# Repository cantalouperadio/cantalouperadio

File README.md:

# Cantaloupe Radio Factory Radio Retrofit Platform

This project contains integrated hardware and firmware to allow stealthy, tight integrations of modern audio technology into factory classic car radios.

TODO lots more to write and explain...

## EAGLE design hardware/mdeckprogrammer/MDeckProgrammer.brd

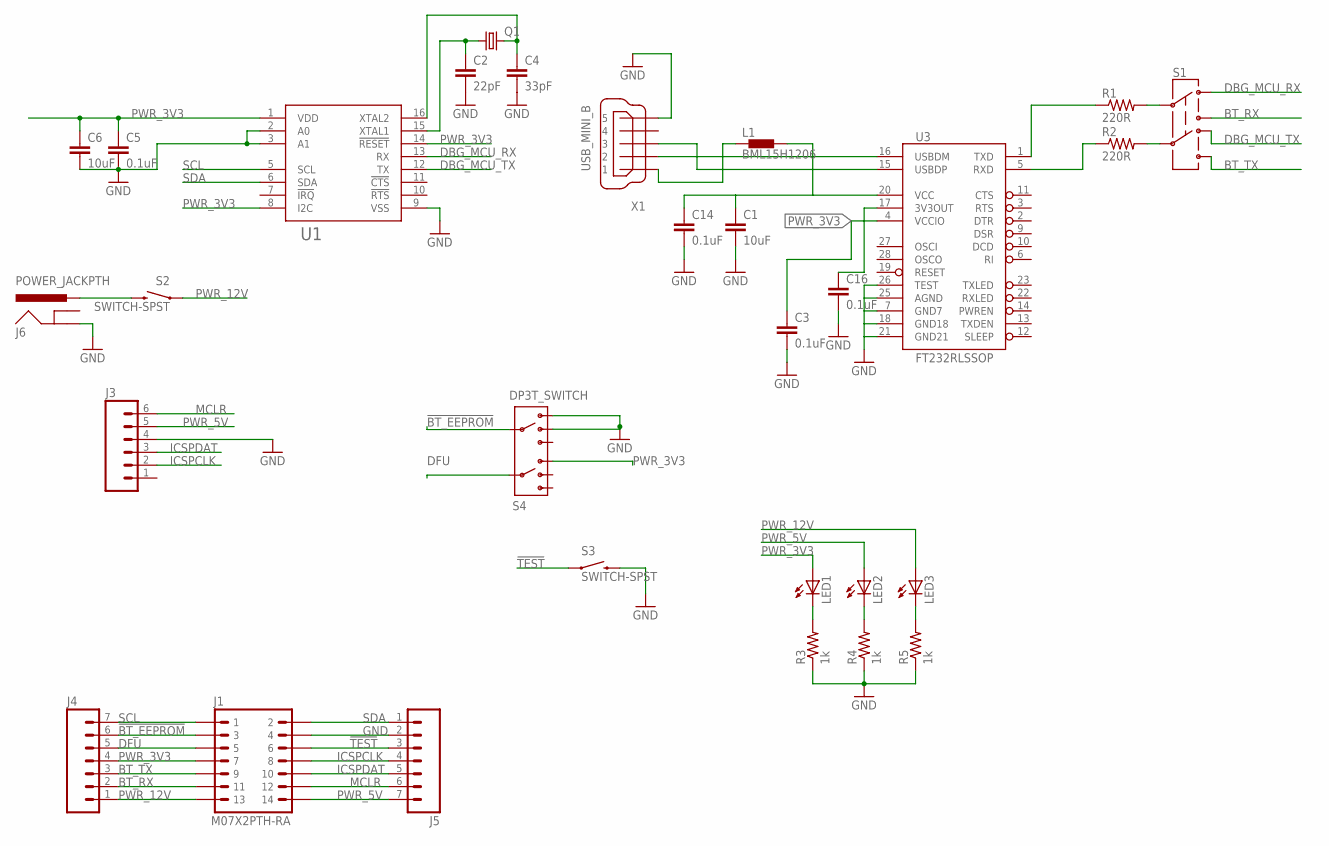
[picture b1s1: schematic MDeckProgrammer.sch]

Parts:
C1, C6: 10uF; 1206
C2: 22pF; 1206
C3, C5, C14, C16: 0.1uF; 1206
C4: 33pF; 1206
J1: M07X2PTH-RA; JST-14-PUD-PTH
J3: M06HARWIN_RA; 1X06_RA
J4, J5: M07; 1X07
J6: POWER_JACKPTH; POWER_JACK_PTH
L1: BML15H1206; 1206
LED1, LED2, LED3: LEDCHIPLED_1206; CHIPLED_1206
Q1: CRYSTALHC49S; HC49/S
R1, R2: 220R; 1206
R3, R4, R5: 1k; 1206
S1: SWITCH-DPDTPTH; MSS22
S2, S3: SWITCH-SPST; GF-123-0054
S4: DP3T_SWITCH; EG2301A
U1: SC16IS740TSSOP16; TSSOP16
U3: FT232RLSSOP; SSOP28DB
X1: USB_MINI_B; USB_MINI_B_PTH

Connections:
!BT_EEPROM: J1.P$3 (3), J4.6, S4.P$3 (COMA)
!TEST: J1.P$6 (6), J5.3, S3.P$1 (1)
BT_RX: J1.P$11 (11), J4.2, S1.3
BT_TX: J1.P$9 (9), J4.3, S1.6
DBG_MCU_RX: S1.1, U1.13 (RX)
DBG_MCU_TX: S1.4, U1.12 (TX)
DFU: J1.P$5 (5), J4.5, S4.P$7 (COMB)
GND: C1.2, C2.2, C3.2, C4.2, C5.2, C6.2, C14.2, C16.2, J1.P$4 (4), J3.4, J5.2, J6.GND, R3.1, R4.1, R5.1, S3.P$2 (2), S4.P$1 (A1), S4.P$2 (A2), U1.2 (A0), U1.3 (A1), U1.9 (VSS), U3.7 (GND7), U3.18 (GND18), U3.21 (GND21), U3.25 (AGND), U3.26 (TEST), X1.5
ICSPCLK: J1.P$8 (8), J3.2, J5.4
ICSPDAT: J1.P$10 (10), J3.3, J5.5
MCLR: J1.P$12 (12), J3.6, J5.6
unnamed: R1.2, S1.2
unnamed: R2.2, S1.5
unnamed: C2.1, Q1.1, U1.15 (XTAL1)
unnamed: C4.1, Q1.2, U1.16 (XTAL2)
unnamed: J6.PWR, S2.P$2 (2)
unnamed: R1.1, U3.1 (TXD)
unnamed: R2.1, U3.5 (RXD)
unnamed: U3.15 (USBDP), X1.3
unnamed: U3.16 (USBDM), X1.2
unnamed: LED1.C, R3.2
unnamed: L1.1, X1.1
unnamed: C1.1, C14.1, L1.2, U3.20 (VCC)
unnamed: LED2.C, R4.2
unnamed: C16.1, U3.17 (3V3OUT)
unnamed: LED3.C, R5.2
PWR_3V3: C3.1, C5.1, C6.1, J1.P$7 (7), J4.4, LED1.A, S4.P$5 (B1), U1.1 (VDD), U1.8 (I2C), U1.14 (!RESET), U3.4 (VCCIO)
PWR_5V: J1.P$14 (14), J3.5, J5.7, LED2.A
PWR_12V: J1.P$13 (13), J4.1, LED3.A, S2.P$1 (1)
SCL: J1.P$1 (1), J4.7, U1.5 (SCL)
SDA: J1.P$2 (2), J5.1, U1.6 (SDA)

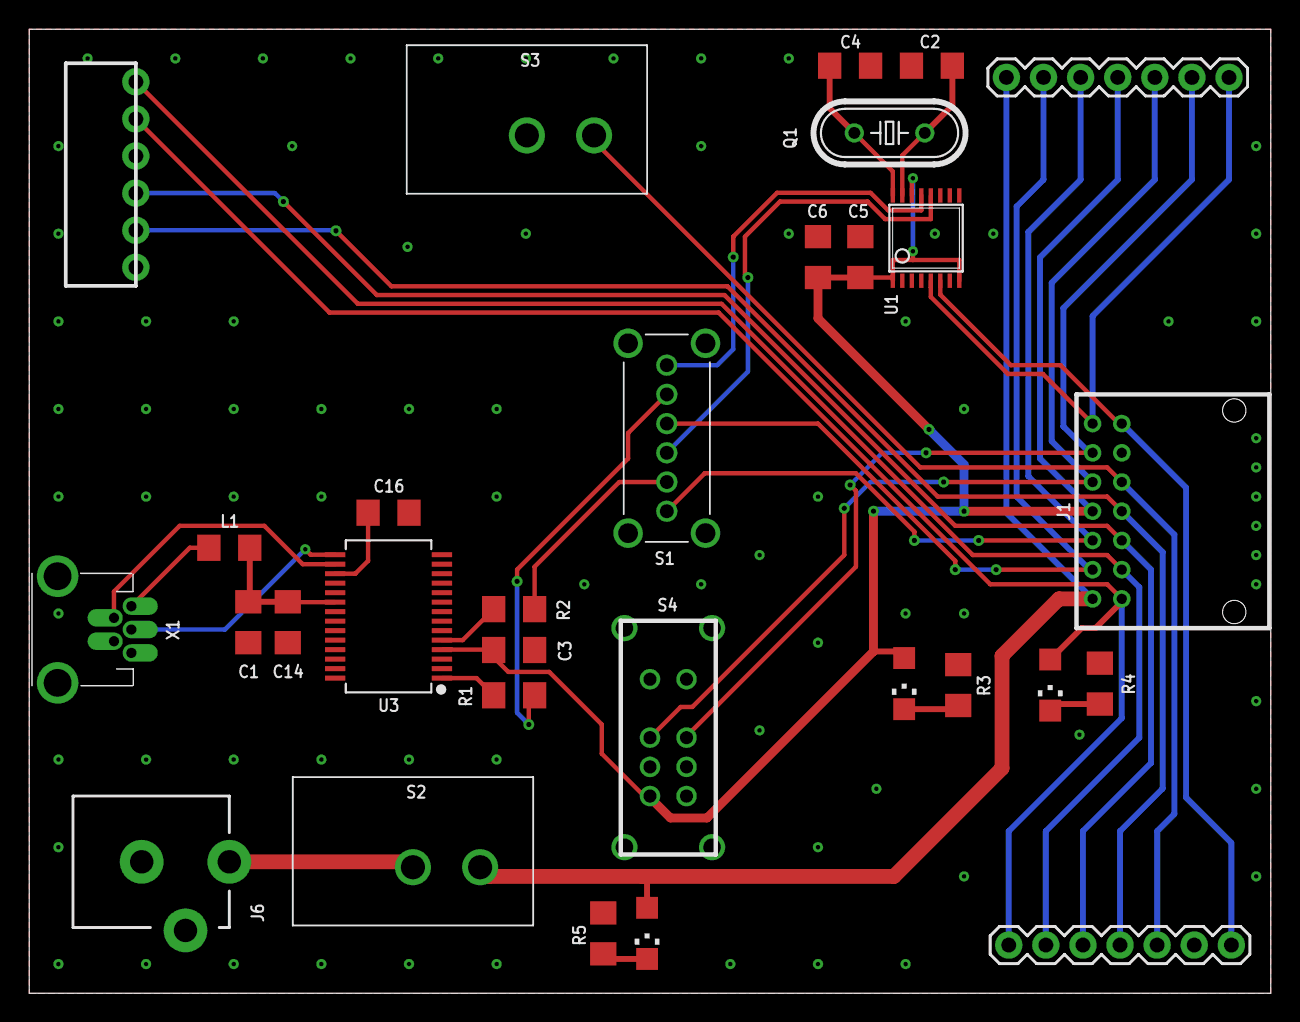
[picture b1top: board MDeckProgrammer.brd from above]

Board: 2 copper layers, 85.0 x 66.0 mm, 30 parts (0 on the bottom side), 31 nets.

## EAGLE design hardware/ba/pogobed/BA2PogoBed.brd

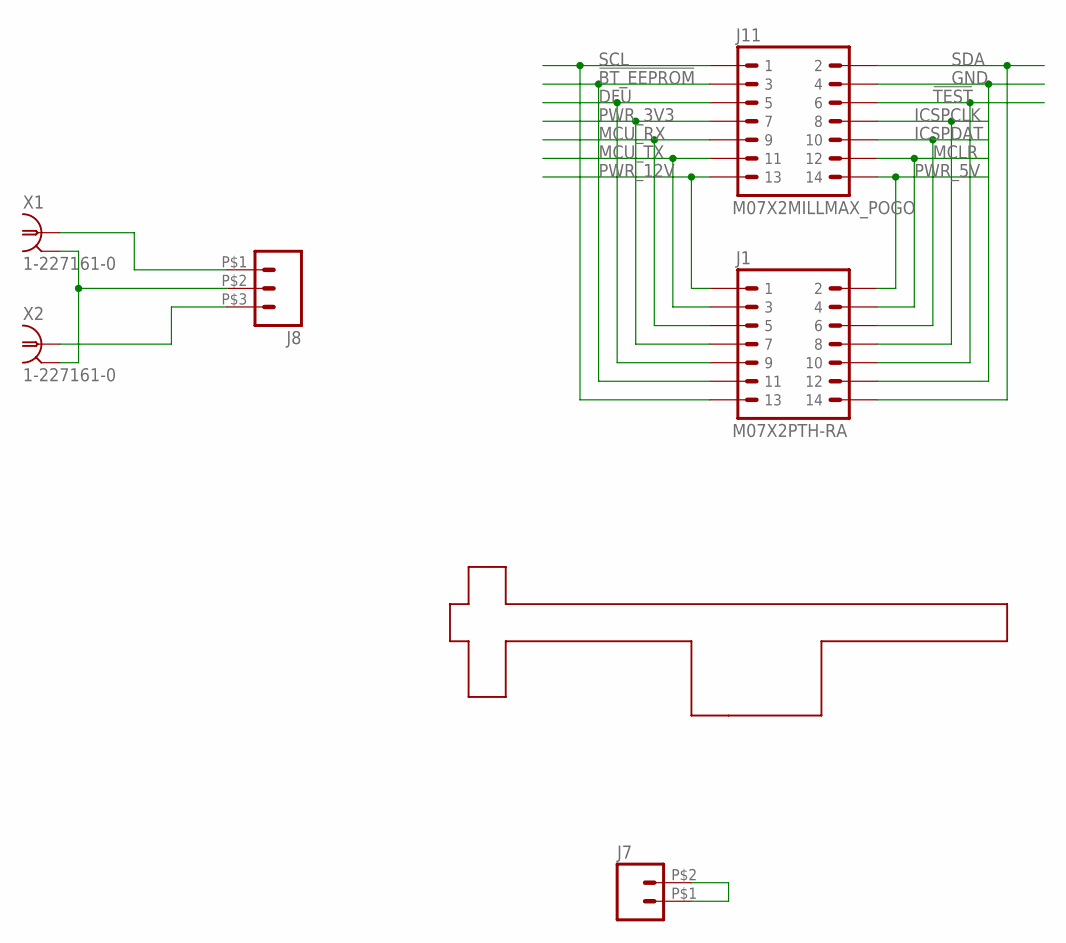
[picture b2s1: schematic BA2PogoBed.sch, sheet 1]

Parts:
J1: M07X2PTH-RA; JST-14-PUD-PTH
J7: M02; MILLMAX_838_1X2
J8: M03; MILLMAX_836_1X3
J11: M07X2MILLMAX_POGO; MILLMAX_838_7X2
M1: TOGGLE_CLAMP_LARGE
X1, X2: 1-227161-0; AMP_227161

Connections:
!BT_EEPROM: J1.P$11 (11), J11.P$3 (3)
!TEST: J1.P$10 (10), J11.P$6 (6)
DFU: J1.P$9 (9), J11.P$5 (5)
GND: J1.P$12 (12), J11.P$4 (4)
ICSPCLK: J1.P$8 (8), J11.P$8 (8)
ICSPDAT: J1.P$6 (6), J11.P$10 (10)
MCLR: J1.P$4 (4), J11.P$12 (12)
MCU_RX: J1.P$5 (5), J11.P$9 (9)
MCU_TX: J1.P$3 (3), J11.P$11 (11)
unnamed: J7.P$1 (1), J7.P$2 (2)
unnamed: J8.P$2 (2), X1.2, X2.2
unnamed: J8.P$1 (1), X1.1
unnamed: J8.P$3 (3), X2.1
PWR_3V3: J1.P$7 (7), J11.P$7 (7)
PWR_5V: J1.P$2 (2), J11.P$14 (14)
PWR_12V: J1.P$1 (1), J11.P$13 (13)
SCL: J1.P$13 (13), J11.P$1 (1)
SDA: J1.P$14 (14), J11.P$2 (2)

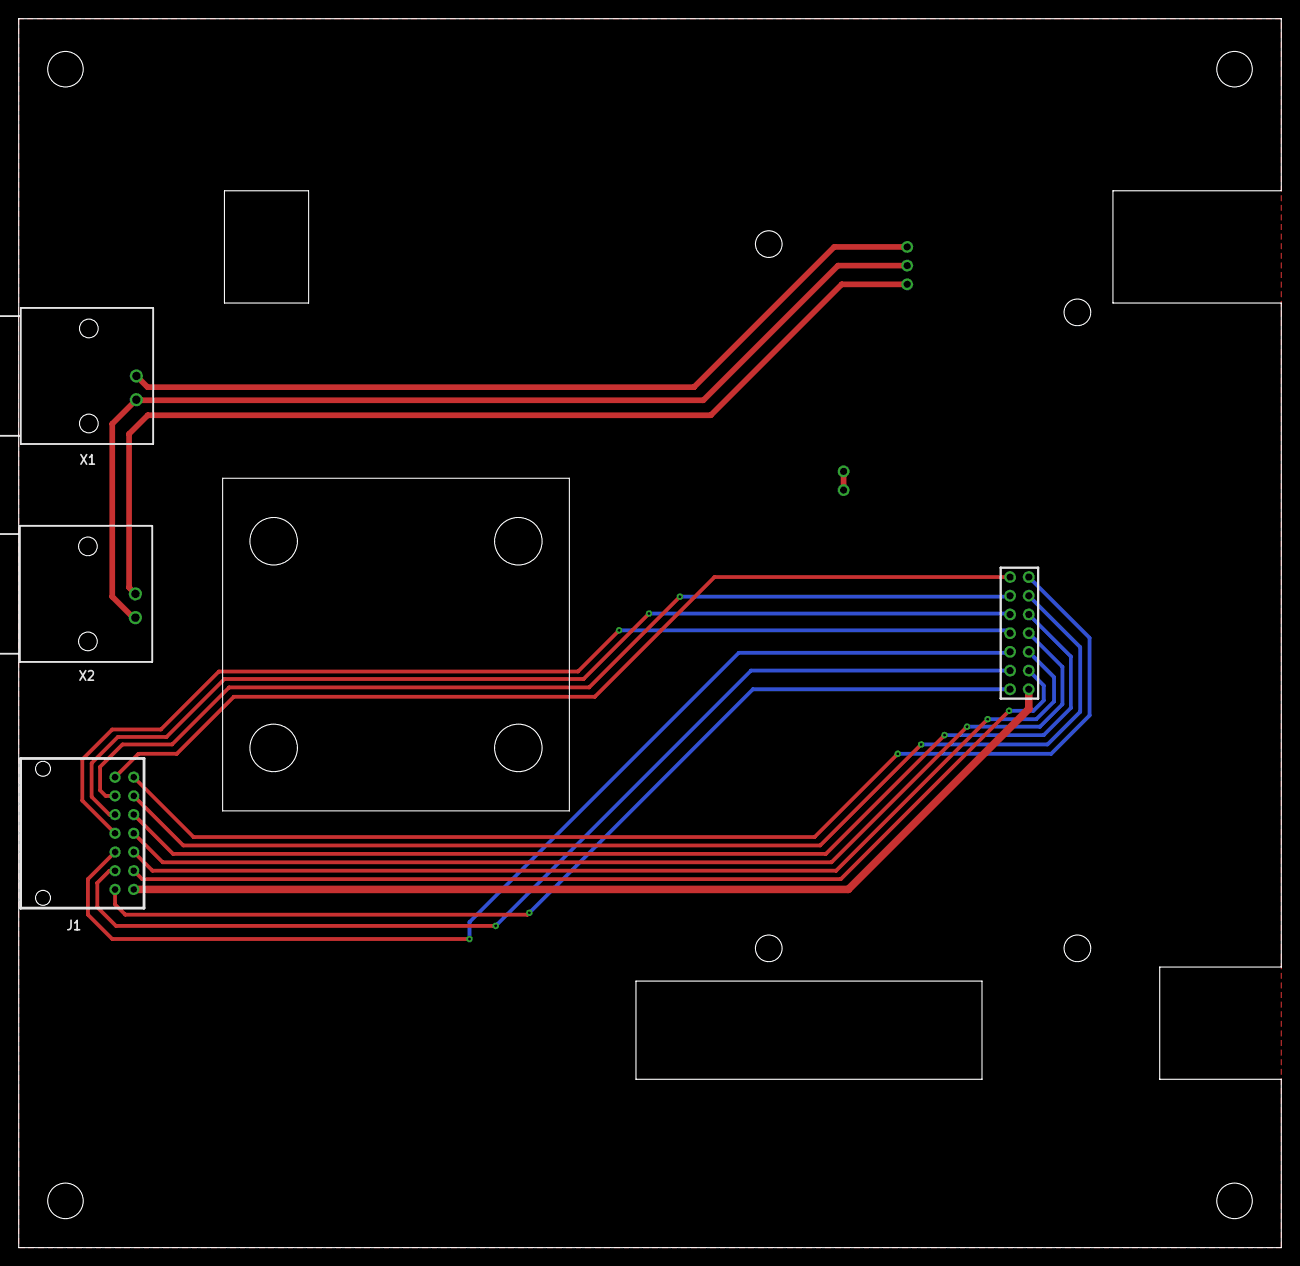
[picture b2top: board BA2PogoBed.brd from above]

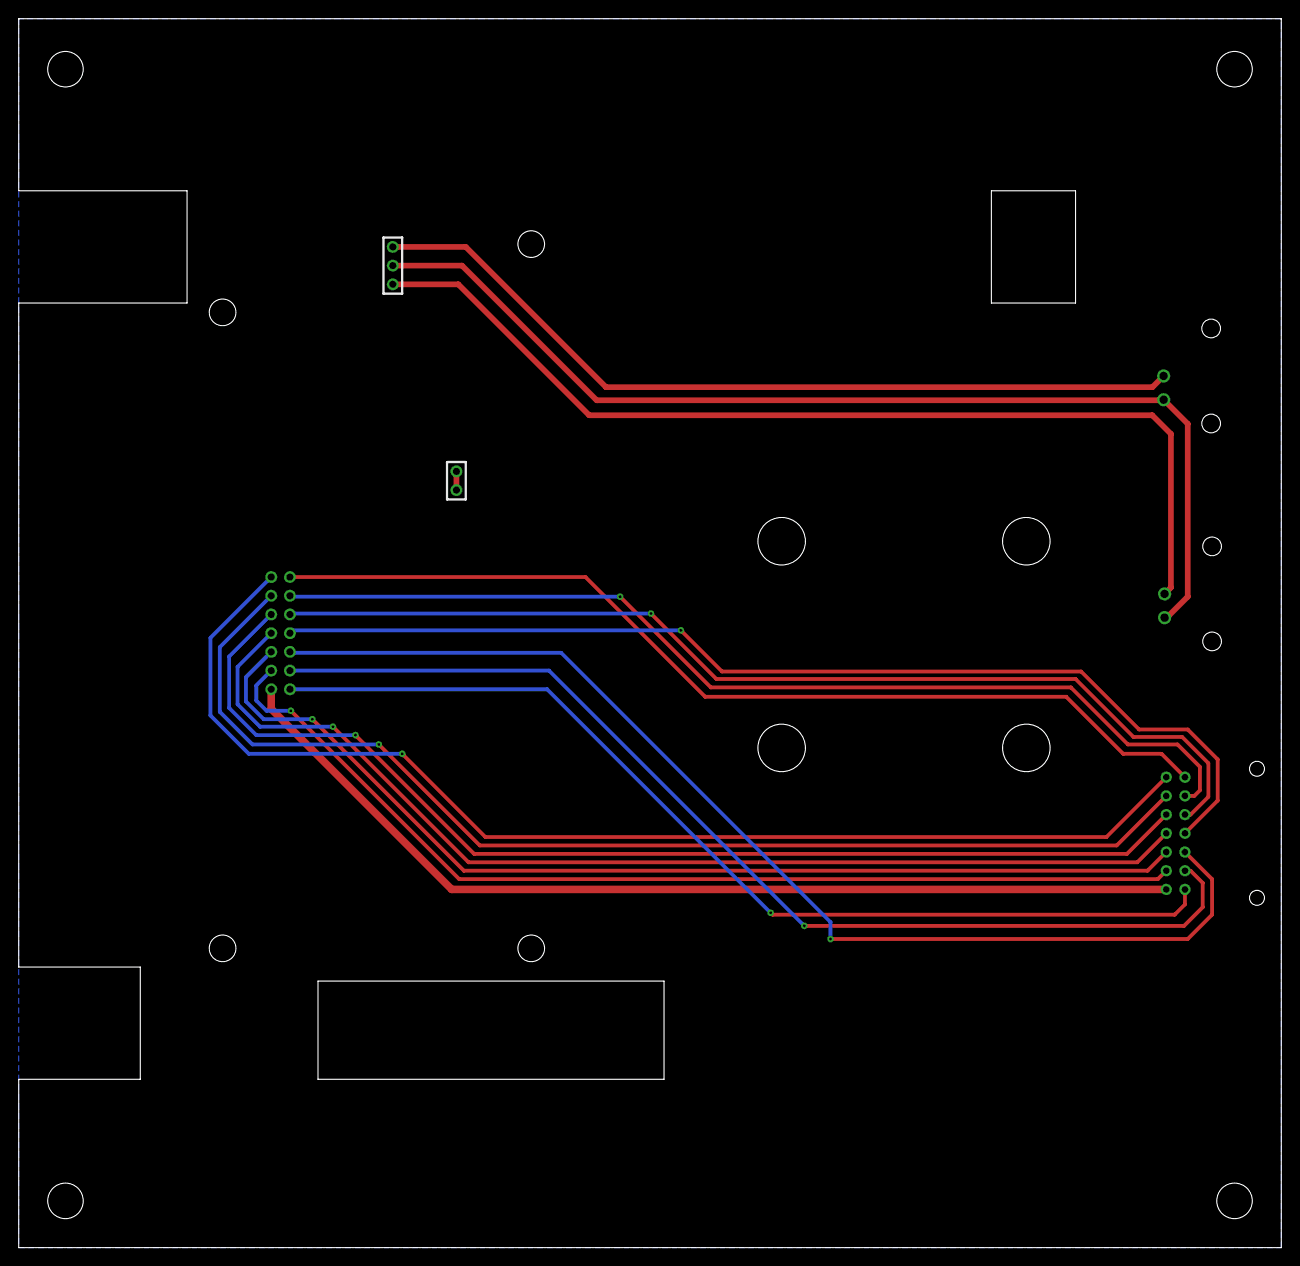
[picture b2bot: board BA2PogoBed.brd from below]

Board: 2 copper layers, 135.0 x 131.4 mm, 7 parts (2 on the bottom side), 18 nets.

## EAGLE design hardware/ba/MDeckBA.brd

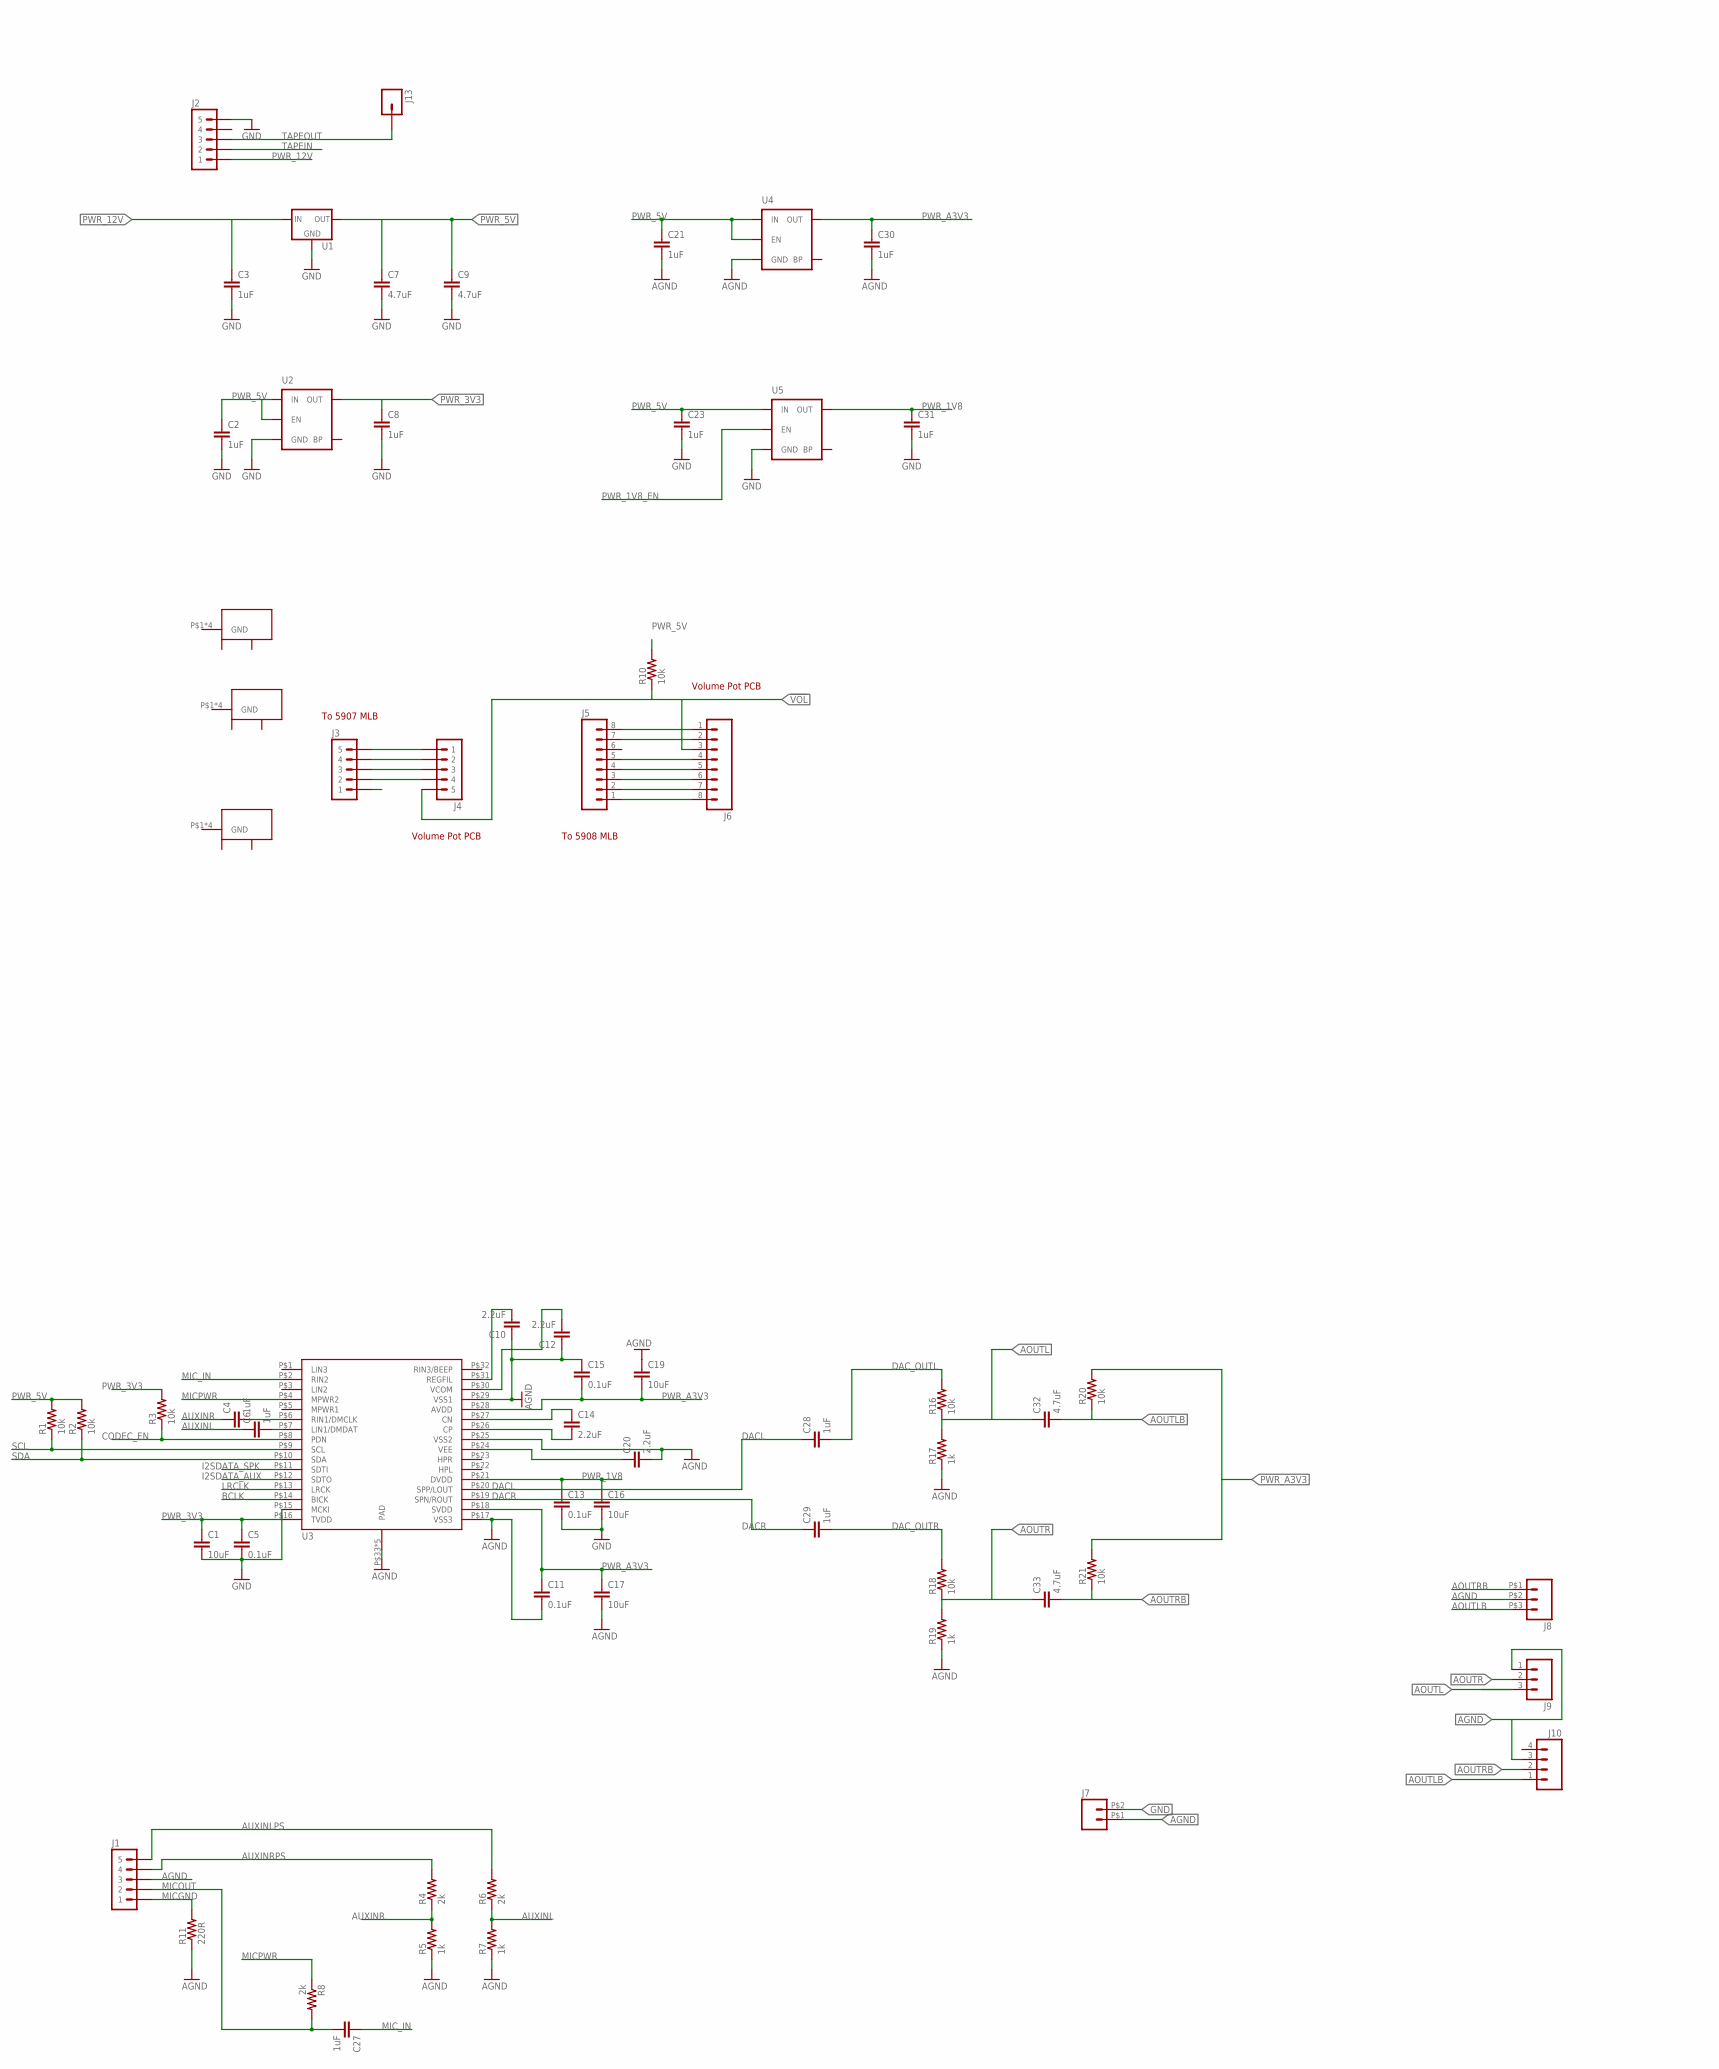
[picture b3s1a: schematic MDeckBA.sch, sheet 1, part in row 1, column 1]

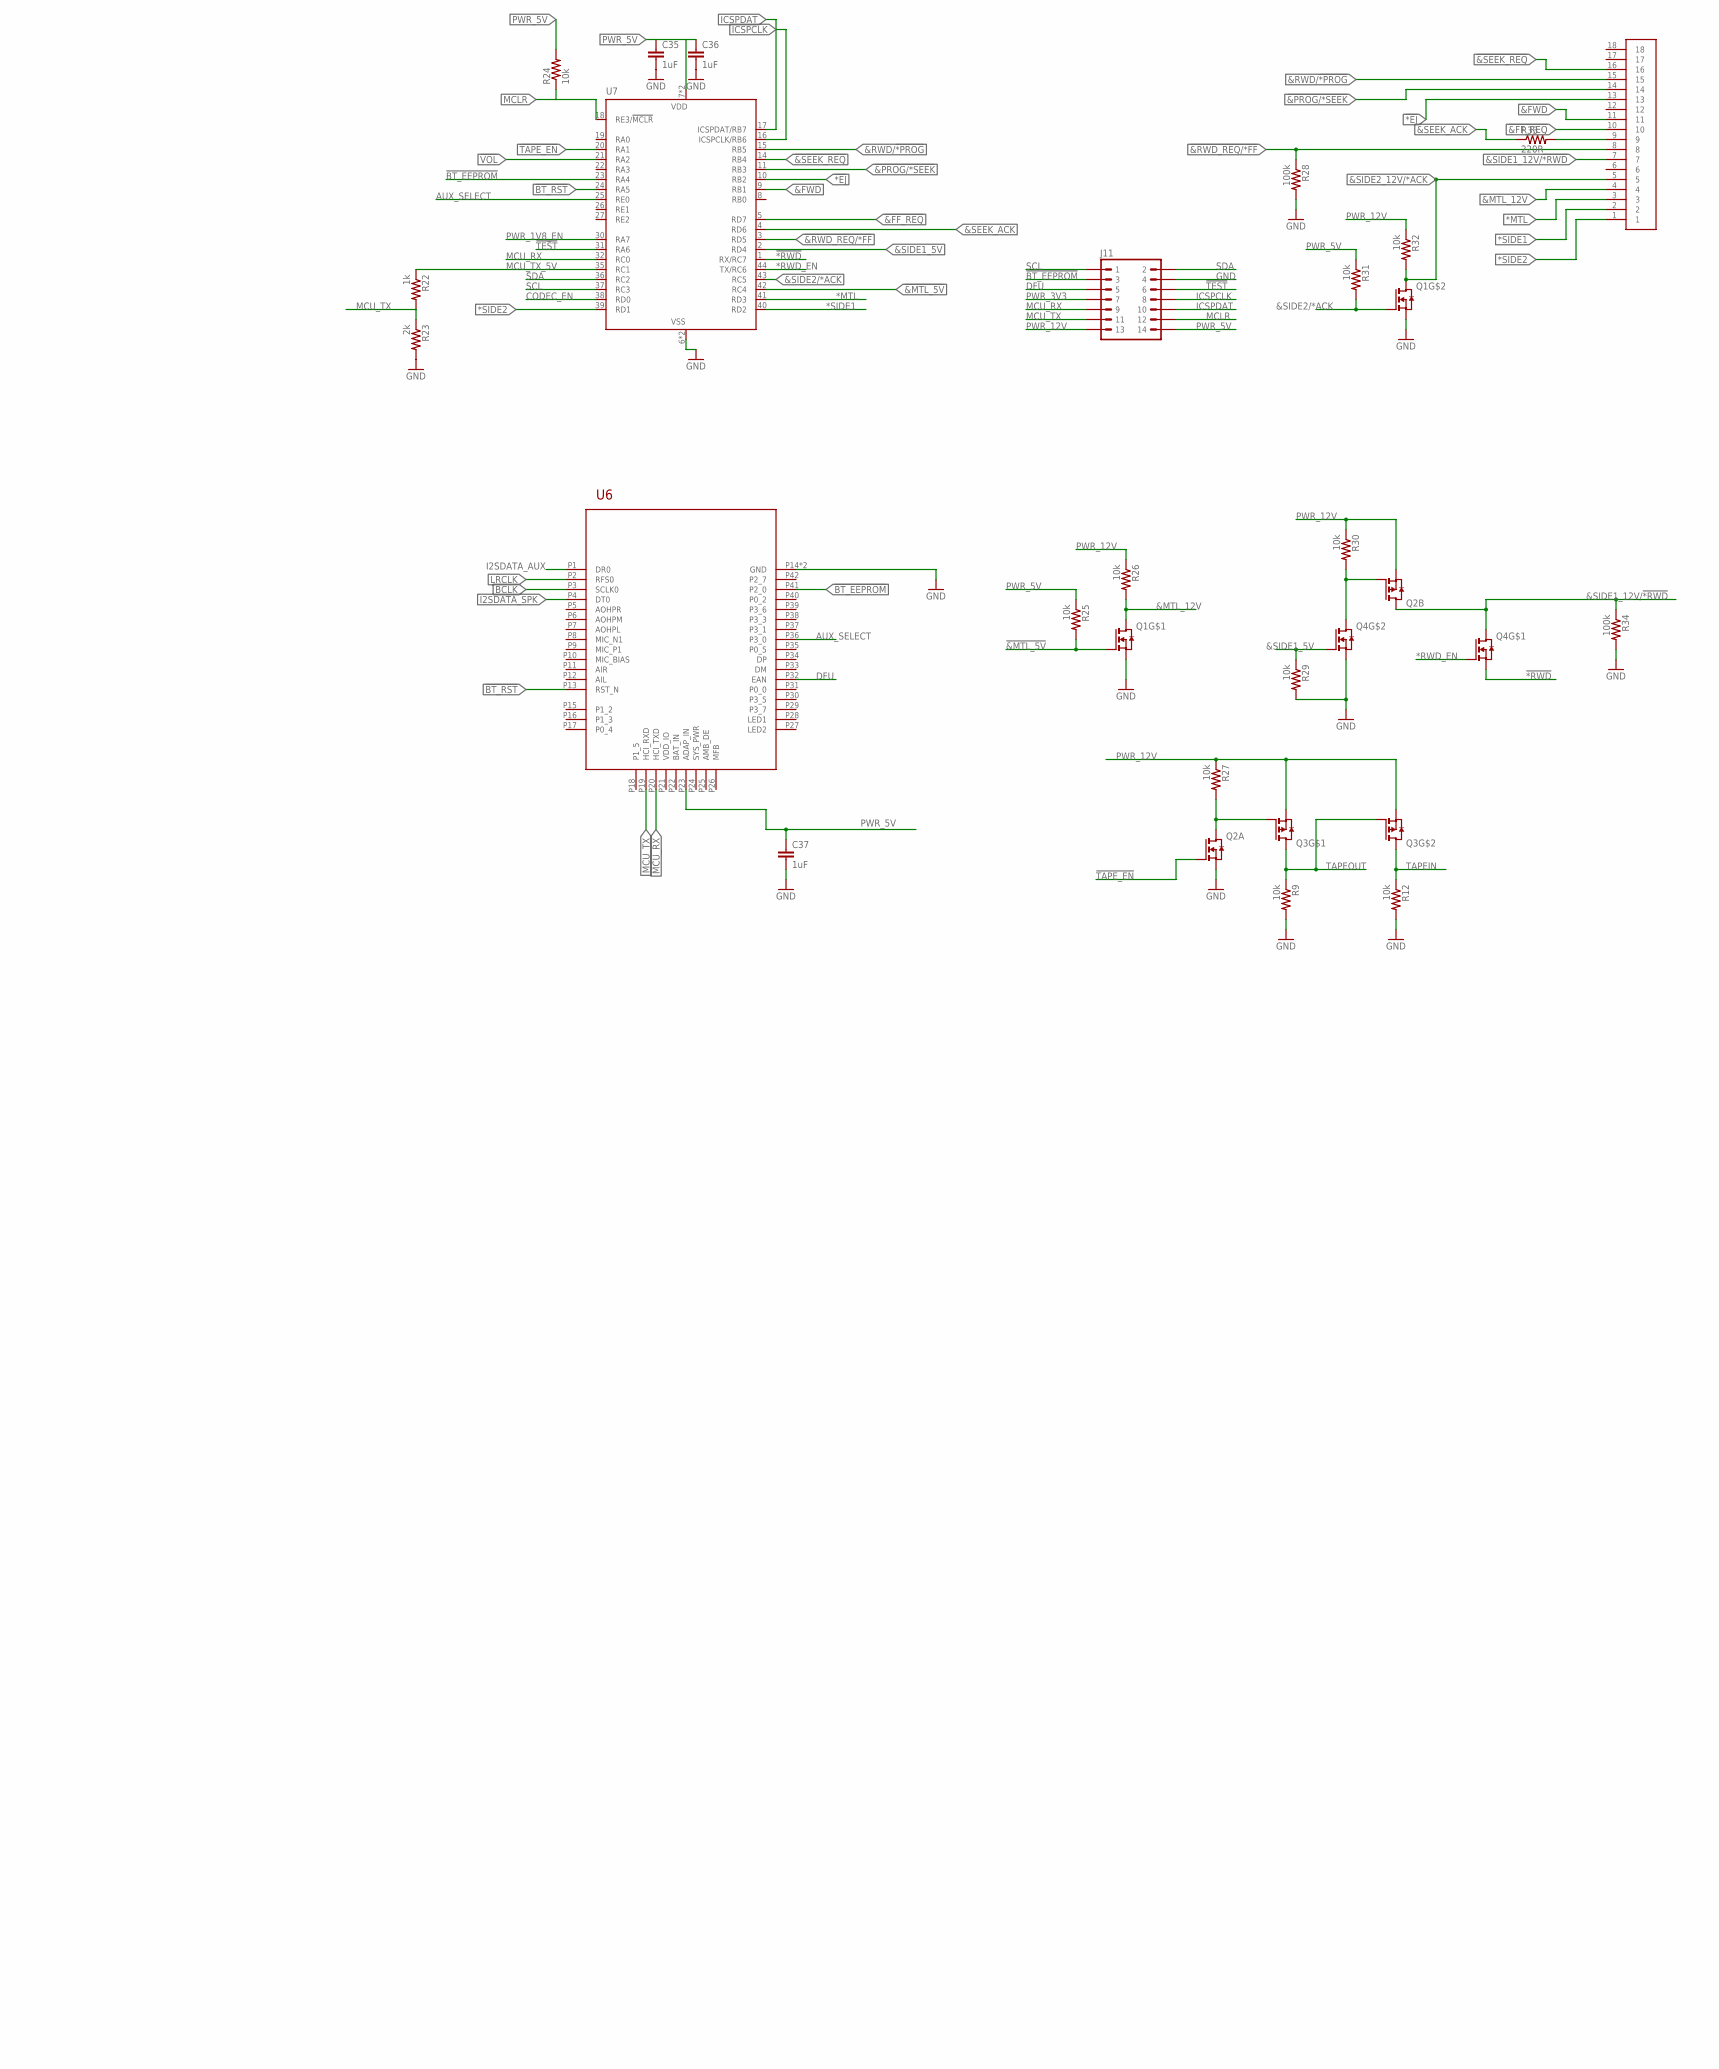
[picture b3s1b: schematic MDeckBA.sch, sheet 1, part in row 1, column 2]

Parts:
C1, C16, C17, C19: 10uF; 0805
C2, C3, C4, C6, C8, C21, C23, C27, C28, C29, C30, C31, C35, C36, C37: 1uF; 0805
C5, C11, C13, C15: 0.1uF; 0805
C7, C9, C32, C33: 4.7uF; 0805
C10, C12, C14, C20: 2.2uF; 0805
J1, J3: M05JST; JST-5-PTH
J2, J4: M05JST-VERT; JST-5-PTH-VERT
J5: JST-PH-8; JST-8-PTH
J6: JST-PH-8-VERT; JST-8-PTH-VERT
J7: M022MM_PADS; 1X02_2MM_PADS
J8: M032MM_PADS; 1X03_2MM_PADS
J9: M03JST-PTH-VERT; JST-3-PTH-VERT
J10: M04JST-PTH-VERT; JST-4-PTH-VERT
J11: M07X2; 2X07_PADS_2MM
J12: MOLEX_0039532184_18_POS_FFC
J13: M01PTH_NO_SILK_YES_STOP; 1X01_NO_SILK
M1, M2, M3: KEYSTONE_7773_SCREW_TERMINAL
Q1, Q4: N_MOSFETSOT-363; SOT363
Q2: PN_MOSFET-FDG6332C_F085SOT363; SOT363
Q3: P_MOSFET_DUAL; SO08
R1, R2, R3, R9, R10, R12, R16, R18, R20, R21, R24, R25, R26, R27, R29, R30, R31, R32: 10k; 0805
R4, R6, R8, R23: 2k; 0805
R5, R7, R17, R19, R22: 1k; 0805
R11: 220R; 2010-RES
R28, R34: 100k; 0805
R33: 220R; 0805
U1: V_REG_SOT223LDL1117; SOT223
U2: V_REG_LDOMIC5317SMD; SOT23-5
U3: AK4951; QFN32_0.4MM
U4: V_REG_LDOLDLN025SMD; SOT23-5
U5: V_REG_LDOMIC5317-1.8SMD; SOT23-5
U6: BM64SMD; BM64
U7: PIC16LF18875PIC16LF18877; TQFP44

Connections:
!&FF_REQ: J12.10, U7.5 (RD7)
!&MTL_5V: Q1.2 (G), R25.2, U7.42 (RC4)
!&PROG/*SEEK: J12.14, U7.11 (RB3)
!&RWD_REQ/*FF: J12.8, R28.1, U7.3 (RD5)
!&SEEK_REQ: J12.16, U7.14 (RB4)
!*EJ: J12.13, U7.10 (RB2)
!*RWD: Q4.1 (S), U7.1 (RX/RC7)
!BT_EEPROM: J11.P$3 (3), U6.P41 (P2_0), U7.23 (RA4)
!BT_RST: U6.P13 (RST_N), U7.24 (RA5)
!TAPE_EN: Q2.2 (G), U7.20 (RA1)
!TEST: J11.P$6 (6), U7.31 (RA6)
!VOL: J4.5, J6.3, R10.1, U7.21 (RA2)
&FWD: J12.11, U7.9 (RB1)
&MTL_12V: J12.4, Q1.6 (D), R26.2
&RWD/!*PROG: J12.15, U7.15 (RB5)
&SEEK_ACK: R33.1, U7.4 (RD6)
&SIDE1_5V: Q4.5 (G), R29.1, U7.2 (RD4)
&SIDE1_12V/!*RWD: J12.7, Q2.3 (D), Q4.6 (D), R34.1
&SIDE2/*ACK: Q1.5 (G), R31.2, U7.43 (RC5)
&SIDE2_12V/*ACK: J12.5, Q1.3 (D), R32.2
*MTL: J12.3, U7.41 (RD3)
*RWD_EN: Q4.2 (G), U7.44 (TX/RC6)
*SIDE1: J12.2, U7.40 (RD2)
*SIDE2: J12.1, U7.39 (RD1)
AGND: C10.1, C11.2, C12.1, C15.1, C17.2, C19.1, C20.2, C21.2, C30.2, J1.3, J7.P$1 (1), J8.P$2 (2), J9.1, J10.3, R5.1, R7.1, R11.1, R17.1, R19.1, U3.P$17 (VSS3), U3.P$25 (VSS2), U3.P$29 (VSS1), U3.P$33 (PAD), U3.P$34 (PAD), U3.P$35 (PAD), U3.P$36 (PAD), U3.P$37 (PAD), U4.2 (GND)
AOUTL: C32.1, J9.3, R16.1, R17.2
AOUTLB: C32.2, J8.P$3 (3), J10.1, R20.1
AOUTR: C33.1, J9.2, R18.1, R19.2
AOUTRB: C33.2, J8.P$1 (1), J10.2, R21.1
AUXINL: C6.1, R6.1, R7.2
AUXINLPS: J1.5, R6.2
AUXINR: C4.1, R4.1, R5.2
AUXINRPS: J1.4, R4.2
AUX_SELECT: U6.P36 (P3_0), U7.25 (RE0)
BCLK: U3.P$14 (BICK), U6.P3 (SCLK0)
CODEC_EN: R3.1, U3.P$8 (PDN), U7.38 (RD0)
DACL: C28.1, U3.P$20 (SPP/LOUT)
DACR: C29.1, U3.P$19 (SPN/ROUT)
DAC_OUTL: C28.2, R16.2
DAC_OUTR: C29.2, R18.2
DFU: J11.P$5 (5), U6.P32 (EAN)
GND: C1.2, C2.2, C3.2, C5.2, C7.2, C8.2, C9.2, C13.2, C16.2, C23.2, C31.2, C35.2, C36.2, C37.2, J2.5, J7.P$2 (2), J11.P$4 (4), Q1.1 (S), Q1.4 (S), Q2.1 (S), Q4.4 (S), R9.2, R12.2, R23.2, R28.2, R29.2, R34.2, U1.1 (GND), U2.2 (GND), U3.P$15 (MCKI), U5.2 (GND), U6.P14 (GND), U6.P43 (GND), U7.6 (VSS), U7.29 (VSS)
I2SDATA_AUX: U3.P$12 (SDTO), U6.P1 (DR0)
I2SDATA_SPK: U3.P$11 (SDTI), U6.P4 (DT0)
ICSPCLK: J11.P$8 (8), U7.16 (ICSPCLK/RB6)
ICSPDAT: J11.P$10 (10), U7.17 (ICSPDAT/RB7)
LRCLK: U3.P$13 (LRCK), U6.P2 (RFS0)
MCLR: J11.P$12 (12), R24.1, U7.18 (RE3/!MCLR)
MCU_RX: J11.P$9 (9), U6.P20 (HCI_TXD), U7.32 (RC0)
MCU_TX: J11.P$11 (11), R22.2, R23.1, U6.P19 (HCI_RXD)
MCU_TX_5V: R22.1, U7.35 (RC1)
MICGND: J1.1, R11.2
MICOUT: C27.2, J1.2, R8.2
MICPWR: R8.1, U3.P$4 (MPWR2)
MIC_IN: C27.1, U3.P$2 (RIN2)
unnamed: J12.9, R33.2
unnamed: Q2.5 (G), Q4.3 (D), R30.2
unnamed: C14.2, U3.P$26 (CP)
unnamed: C10.2, U3.P$31 (REGFIL)
unnamed: C20.1, U3.P$24 (VEE)
unnamed: J5.8, J6.1
unnamed: C12.2, U3.P$30 (VCOM)
unnamed: C14.1, U3.P$27 (CN)
unnamed: C6.2, U3.P$7 (LIN1/DMDAT)
unnamed: J5.7, J6.2
unnamed: J5.5, J6.4
unnamed: J5.4, J6.5
unnamed: J5.3, J6.6
unnamed: J5.2, J6.7
unnamed: J5.1, J6.8
unnamed: C4.2, U3.P$6 (RIN1/DMCLK)
unnamed: J3.5, J4.1
unnamed: J3.4, J4.2
unnamed: J3.3, J4.3
unnamed: J3.2, J4.4
PWR_1V8: C13.1, C16.1, C31.1, U3.P$21 (DVDD), U5.5 (OUT)
PWR_1V8_EN: U5.3 (EN), U7.30 (RA7)
PWR_3V3: C1.1, C5.1, C8.1, J11.P$7 (7), R3.2, U2.5 (OUT), U3.P$16 (TVDD)
PWR_5V: C2.1, C7.1, C9.1, C21.1, C23.1, C35.1, C36.1, C37.1, J11.P$14 (14), R1.2, R2.2, R10.2, R24.2, R25.1, R31.1, U1.2 (OUT), U1.4 (OUT), U2.1 (IN), U2.3 (EN), U4.1 (IN), U4.3 (EN), U5.1 (IN), U6.P23 (ADAP_IN), U7.7 (VDD), U7.28 (VDD)
PWR_12V: C3.1, J2.1, J11.P$13 (13), Q2.4 (S), Q3.1 (S), Q3.3 (S), R26.1, R27.1, R30.1, R32.1, U1.3 (IN)
PWR_A3V3: C11.1, C15.2, C17.1, C19.2, C30.1, R20.2, R21.2, U3.P$18 (SVDD), U3.P$28 (AVDD), U4.5 (OUT)
SCL: J11.P$1 (1), R1.1, U3.P$9 (SCL), U7.37 (RC3)
SDA: J11.P$2 (2), R2.1, U3.P$10 (SDA), U7.36 (RC2)
TAPEIN: J2.2, Q3.5 (D), Q3.6 (D), R12.1
TAPEINSIG: Q2.6 (D), Q3.2 (G), R27.2
TAPEOUT: J2.3, J13.1, Q3.4 (G), Q3.7 (D), Q3.8 (D), R9.1

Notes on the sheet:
Volume Pot PCB
To 5908 MLB
To 5907 MLB

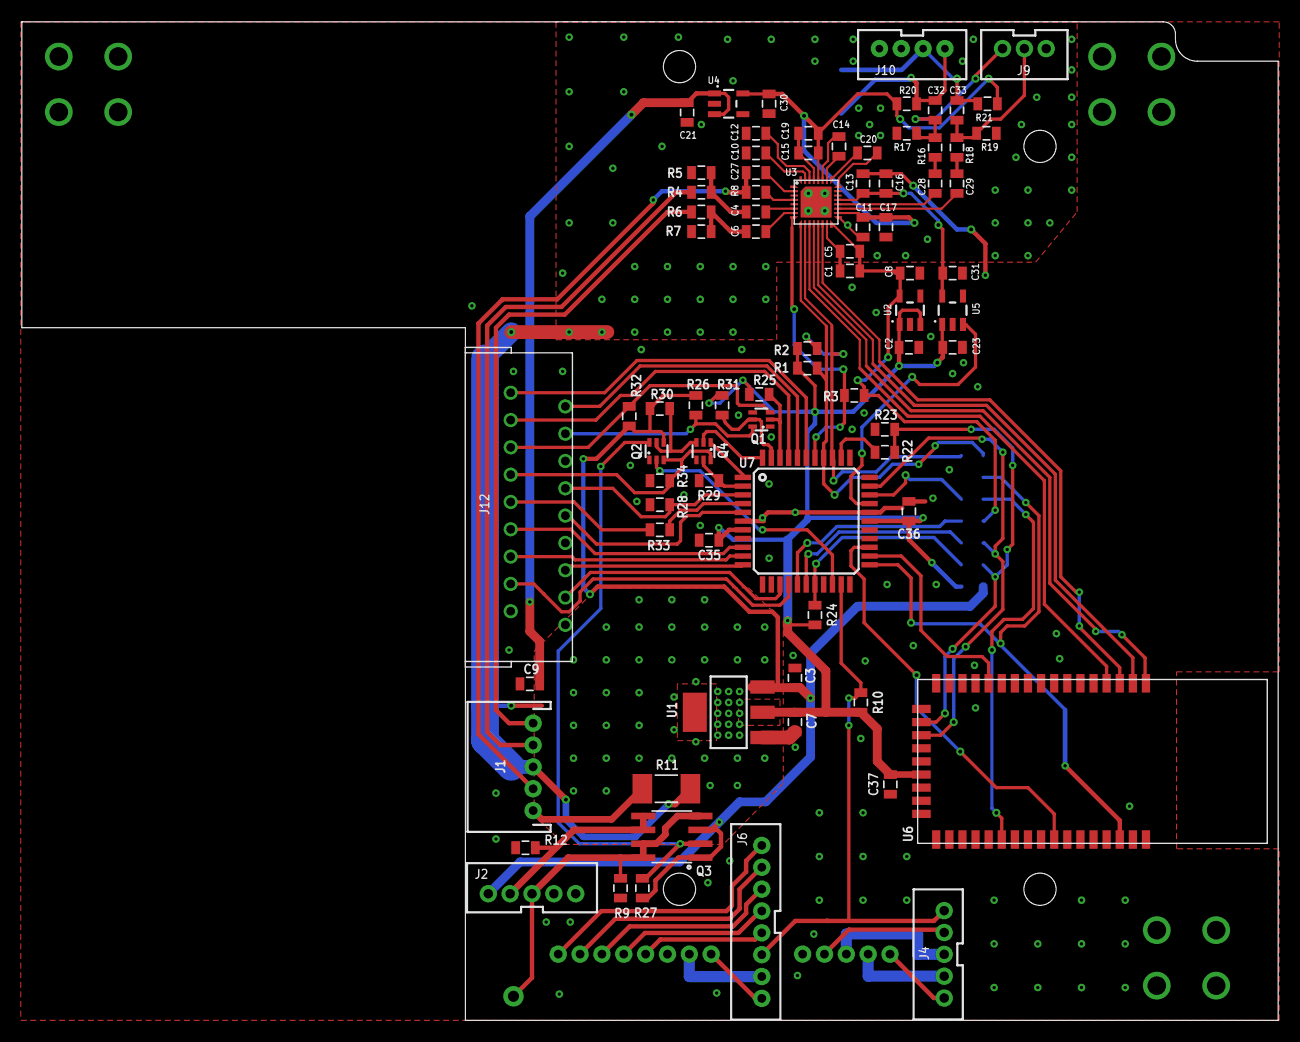
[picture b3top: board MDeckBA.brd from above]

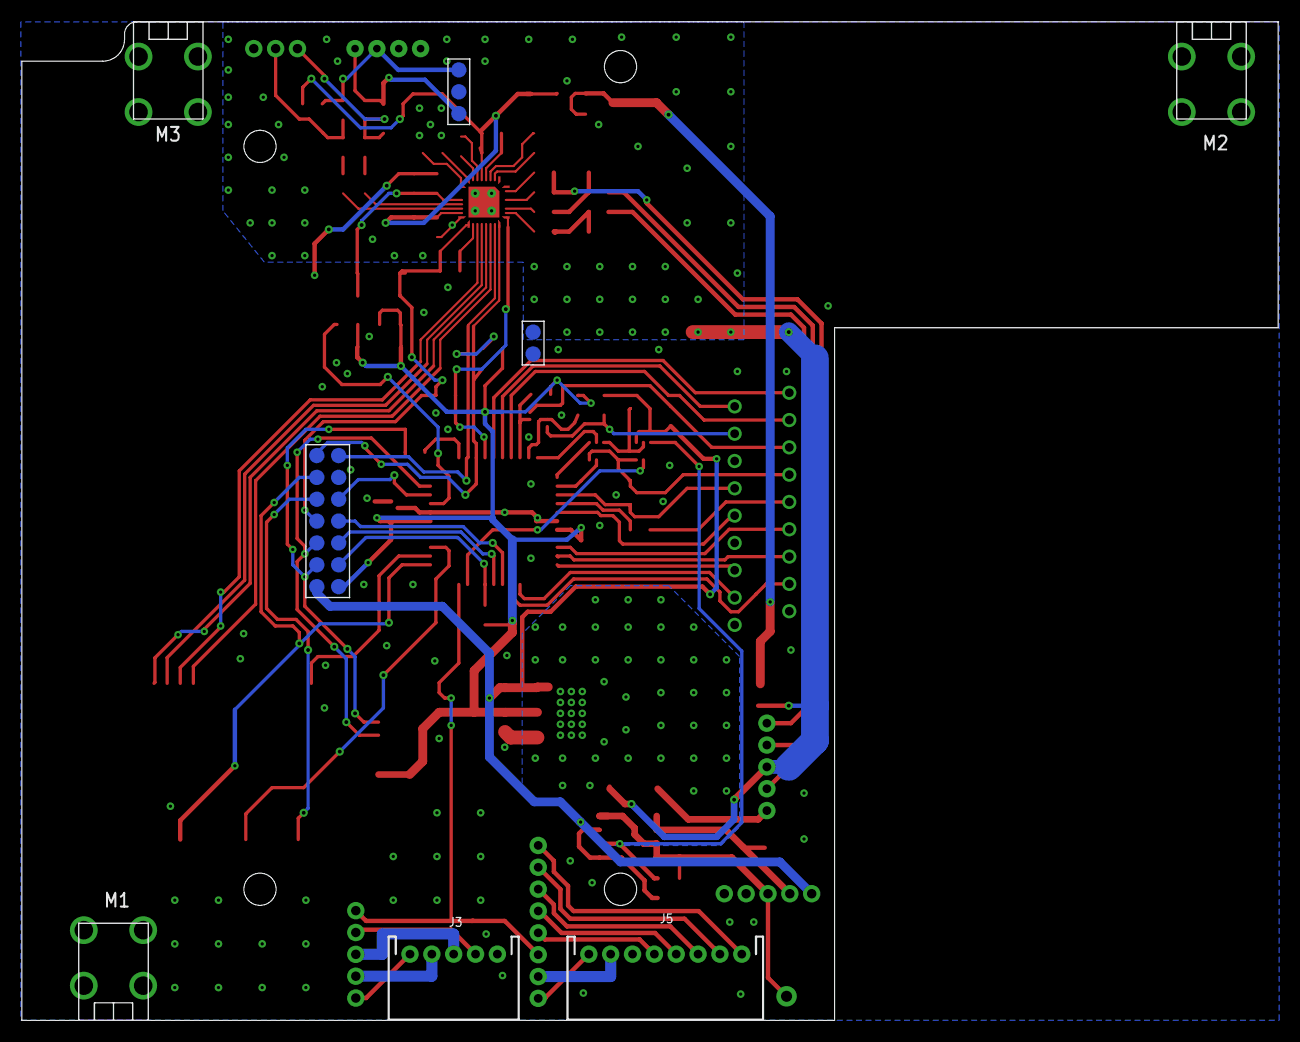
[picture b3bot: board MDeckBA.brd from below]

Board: 2 copper layers, 115.0 x 91.4 mm, 89 parts (7 on the bottom side), 86 nets.

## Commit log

2020-05-11 Initial commit of gitignore, license, and eagle cad, gerbers, and bm64 config for ba-2 rev9
2020-05-11 Adding readme and license
2020-05-11 Actually add gerbers
2020-05-11 Update gitignore
2020-06-08 Updated FW assets to versions that actually shipped with BA2r9
2020-07-01 Adding BA-2 aux board BOMs and more work on readme
2020-07-01 Actually update readme
2020-07-01 Typos
2020-07-01 Adding eagle files for BA2 aux boards
2020-07-01 BA-2 programming readme edits

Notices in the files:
hardware/mdeckprogrammer/MDeckProgrammer.brd:
Copyright 2018 Cantaloupe Radio LLC
parts and their libraries:
SparkFun-Connectors: Licensing: Creative Commons ShareAlike 4.0 International - https://creativecommons.org/licenses/by-sa/4.0
